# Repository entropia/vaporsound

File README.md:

# vaporsound

Our custom audio amplifier for the hackerspace

## hardware

The vaporsound board can drive two speakers with up to 50W each and has an analog stereo input.
It is connected to a beaglebone black which provides an ethernet port.
The vaporsound board needs a 24V power supply and provides 5V to the beaglebone black.

The hardware is designed in Eagle.

## mechanical

The vaporsound case is designed in Rhino3D and can be lasercut from 4mm wood.

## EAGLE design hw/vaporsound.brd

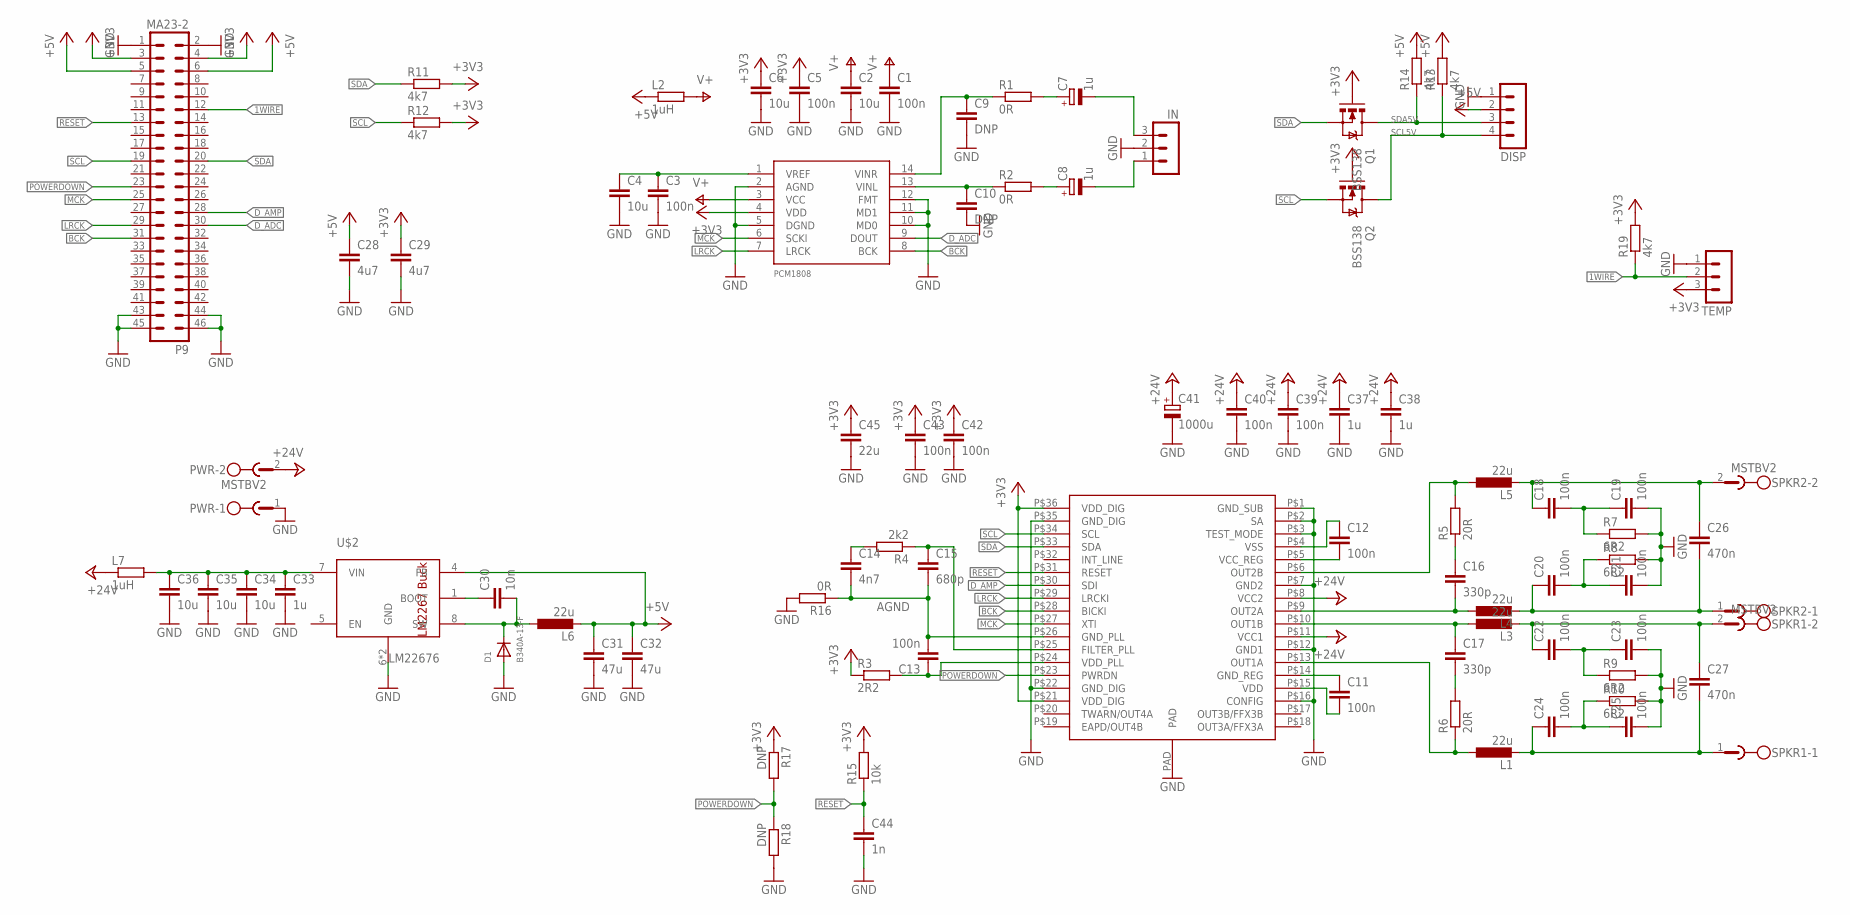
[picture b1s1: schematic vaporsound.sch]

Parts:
C1, C3, C5, C11, C12, C13, C18, C19, C20, C21, C22, C23, C24, C25, C39, C40, C42, C43: 100n; C0603
C2, C4, C6: 10u; C0805
C7, C8: 1u; E2-5
C9, C10: DNP; C0603
C14: 4n7; C0603
C15: 680p; C0603
C16, C17: 330p; C0603
C26, C27: 470n; C050-045X075
C28, C29: 4u7; C0805
C30: 10n; C0603
C31, C32: 47u; C1206
C33: 1u; C0805
C34, C35, C36: 10u; C1206
C37, C38: 1u; C1206
C41: 1000u; E5-10,5
C44: 1n; C0603
C45: 22u; C1206
D1: B340A-13-F; SMADIODE
DISP: MA04-1
IN: MA03-1
L1, L3, L4, L5: 22u; SRR1210
L2, L7: 1uH; R0805
L6: 22u; IHLP-3232DZ-11
P9: MA23-2
PWR: MSTBV2
Q1, Q2: BSS138; SOT23-3
R1, R2, R16: 0R; R0603
R3: 2R2; R0603
R4: 2k2; R0603
R5, R6: 20R; R1206
R7, R8, R9, R10: 6R2; R1206
R11, R12, R13, R14, R19: 4k7; R0603
R15: 10k; R0603
R17, R18: DNP; R0603
SPKR1, SPKR2: MSTBV2
TEMP: MA03-1
U$1: STA350BW; POWERSSO-36
U$2: LM22676; DDA0008B
U$3: PCM1808; TSSOP14

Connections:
1WIRE: P9.12, R19.1, TEMP.2
24V_DIGITAL: C33.1, C34.1, C35.1, C36.1, L7.2, U$2.7 (VIN)
+3V3: C5.1, C6.1, C29.1, C42.1, C43.1, C45.1, P9.3, P9.4, Q1.1 (G), Q2.1 (G), R3.1, R11.2, R12.2, R15.2, R17.1, R19.2, TEMP.3, U$1.P$21 (VDD_DIG), U$1.P$36 (VDD_DIG), U$3.4 (VDD)
+5V: C28.1, C31.1, C32.1, DISP.2, L2.1, L6.P$2 (2), P9.5, P9.6, R13.2, R14.2, U$2.4 (FB)
+24V: C37.1, C38.1, C39.1, C40.1, C41.+, L7.1, PWR.2, U$1.P$8 (VCC2), U$1.P$11 (VCC1)
ADC_VREF: C3.1, C4.1, U$3.1 (VREF)
AGND: C13.2, C14.2, C15.2, R16.1, U$1.P$26 (GND_PLL)
BCK: P9.31, U$1.P$28 (BICKI), U$3.8 (BCK)
BOOST: C30.1, U$2.1 (BOOT)
C_LEFT: C8.+, R2.2
C_RIGHT: C7.+, R1.2
D_ADC: P9.30, U$3.9 (DOUT)
D_AMP: P9.28, U$1.P$30 (SDI)
FILTER_PLL: C15.1, R4.1, U$1.P$25 (FILTER_PLL)
GND: C1.2, C2.2, C3.2, C4.2, C5.2, C6.2, C9.2, C10.2, C19.2, C21.2, C23.2, C25.2, C28.2, C29.2, C31.2, C32.2, C33.2, C34.2, C35.2, C36.2, C37.2, C38.2, C39.2, C40.2, C41.-, C42.2, C43.2, C44.2, C45.2, D1.A, DISP.1, IN.2, P9.1, P9.2, P9.43, P9.44, P9.45, P9.46, PWR.1, R7.2, R8.2, R9.2, R10.2, R16.2, R18.2, TEMP.1, U$1.P$1 (GND_SUB), U$1.P$2 (SA), U$1.P$3 (TEST_MODE), U$1.P$7 (GND2), U$1.P$12 (GND1), U$1.P$16 (CONFIG), U$1.P$22 (GND_DIG), U$1.P$35 (GND_DIG), U$1.PAD, U$2.6 (GND), U$2.EPAD (GND), U$3.2 (AGND), U$3.5 (DGND), U$3.10 (MD0), U$3.11 (MD1), U$3.12 (FMT)
GND_REG: C11.1, U$1.P$14 (GND_REG)
LEFT_INPUT: C8.-, IN.1
LRCK: P9.29, U$1.P$29 (LRCKI), U$3.7 (LRCK)
MCK: P9.25, U$1.P$27 (XTI), U$3.6 (SCKI)
unnamed: C17.2, R6.2
unnamed: C14.1, R4.2
unnamed: C16.1, R5.1
unnamed: C18.2, C19.1, R7.1
unnamed: C20.2, C21.1, R8.1
unnamed: C24.2, C25.1, R10.1
unnamed: C22.2, C23.1, R9.1
OUT1A: L1.P$1 (1), R6.1, U$1.P$13 (OUT1A)
OUT1B: C17.1, L3.P$1 (1), U$1.P$10 (OUT1B)
OUT2A: C16.2, L4.P$1 (1), U$1.P$9 (OUT2A)
OUT2B: L5.P$1 (1), R5.2, U$1.P$6 (OUT2B)
POWERDOWN: P9.23, R17.2, R18.1, U$1.P$23 (PWRDN)
RESET: C44.1, P9.13, R15.1, U$1.P$31 (RESET)
RIGHT_INPUT: C7.-, IN.3
SCL: P9.19, Q2.2 (S), R12.1, U$1.P$34 (SCL)
SCL5V: DISP.4, Q2.3 (D), R13.1
SDA: P9.20, Q1.2 (S), R11.1, U$1.P$33 (SDA)
SDA5V: DISP.3, Q1.3 (D), R14.1
SPKR1A: C24.1, C27.2, L1.P$2 (2), SPKR1.1
SPKR1B: C22.1, C27.1, L3.P$2 (2), SPKR1.2
SPKR2A: C20.1, C26.2, L4.P$2 (2), SPKR2.1
SPKR2B: C18.1, C26.1, L5.P$2 (2), SPKR2.2
SW: C30.2, D1.C, L6.P$1 (1), U$2.8 (SW)
V+: C1.1, C2.1, L2.2, U$3.3 (VCC)
VCC_REG: C12.2, U$1.P$5 (VCC_REG)
VDD: C11.2, U$1.P$15 (VDD)
VDD_PLL: C13.1, R3.2, U$1.P$24 (VDD_PLL)
VIN_L: C10.1, R2.1, U$3.13 (VINL)
VIN_R: C9.1, R1.1, U$3.14 (VINR)
VSS: C12.1, U$1.P$4 (VSS)

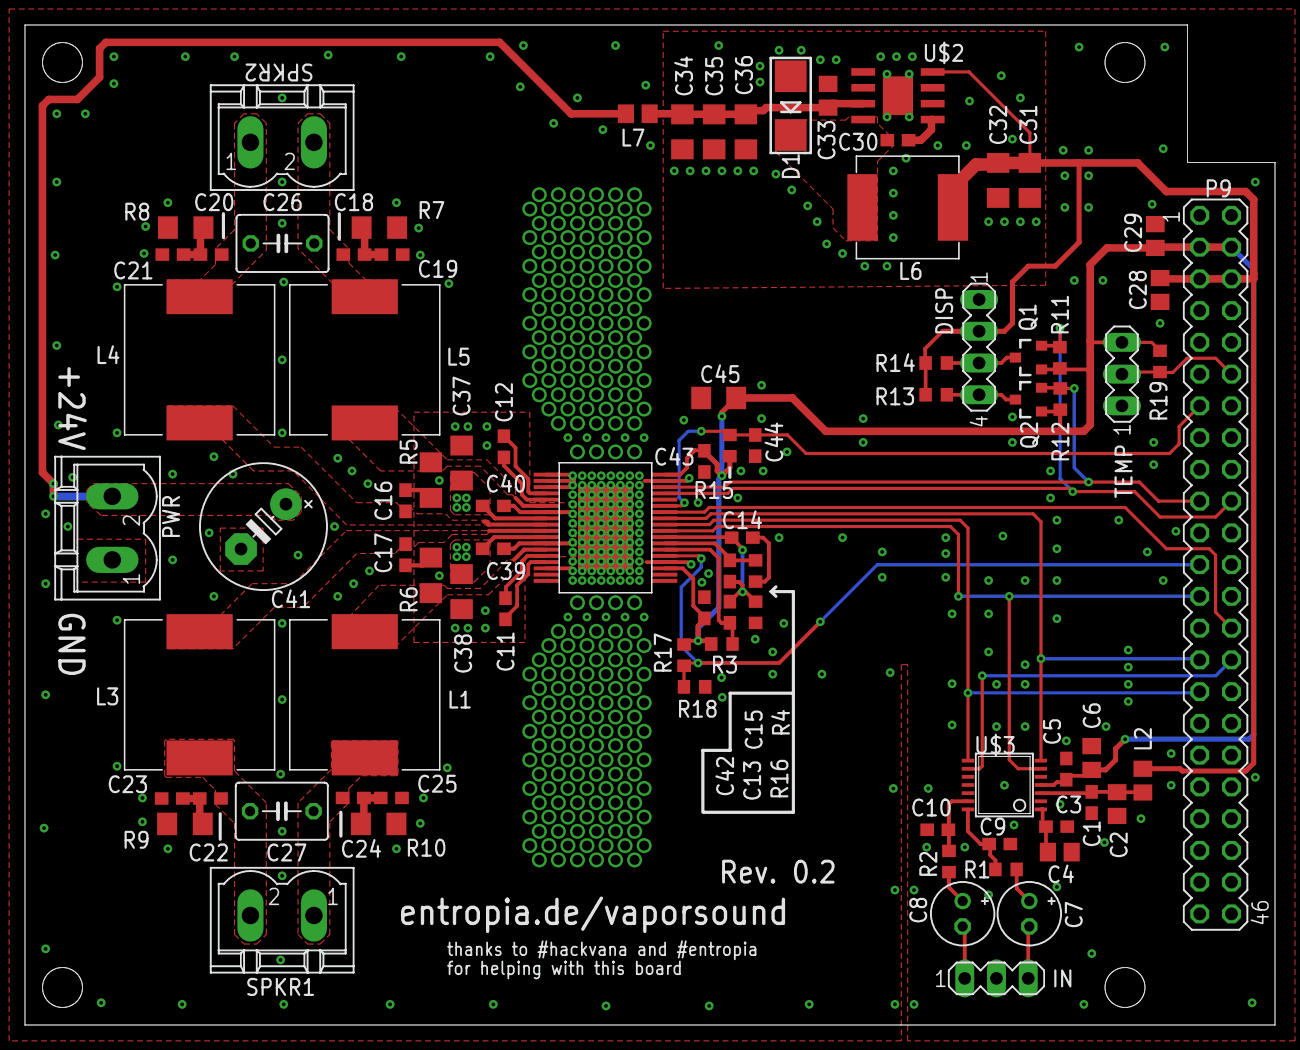
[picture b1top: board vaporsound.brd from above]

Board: 2 copper layers, 100.0 x 80.0 mm, 84 parts (0 on the bottom side), 49 nets.

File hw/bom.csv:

;Part;Value;Device;Package;Description;MF;MPN;OC_FARNELL;OC_NEWARK;PROD_ID
X;R1;0R;R-EU_R0603;R0603;RESISTOR, European symbol;;;;;
X;R2;0R;R-EU_R0603;R0603;RESISTOR, European symbol;;;;;
X;R16;0R;R-EU_R0603;R0603;RESISTOR, European symbol;;;;;
X;C41;1000u;CPOL-EUE5-10.5;E5-10,5;POLARIZED CAPACITOR, European symbol;;;;;
vorhanden;C1;100n;C-EUC0603;C0603;CAPACITOR, European symbol;;;;;
vorhanden;C3;100n;C-EUC0603;C0603;CAPACITOR, European symbol;;;;;
vorhanden;C5;100n;C-EUC0603;C0603;CAPACITOR, European symbol;;;;;
vorhanden;C11;100n;C-EUC0603;C0603;CAPACITOR, European symbol;;;;;
vorhanden;C12;100n;C-EUC0603;C0603;CAPACITOR, European symbol;;;;;
vorhanden;C13;100n;C-EUC0603;C0603;CAPACITOR, European symbol;;;;;
vorhanden;C18;100n;C-EUC0603;C0603;CAPACITOR, European symbol;;;;;
vorhanden;C19;100n;C-EUC0603;C0603;CAPACITOR, European symbol;;;;;
vorhanden;C20;100n;C-EUC0603;C0603;CAPACITOR, European symbol;;;;;
vorhanden;C21;100n;C-EUC0603;C0603;CAPACITOR, European symbol;;;;;
vorhanden;C22;100n;C-EUC0603;C0603;CAPACITOR, European symbol;;;;;
vorhanden;C23;100n;C-EUC0603;C0603;CAPACITOR, European symbol;;;;;
vorhanden;C24;100n;C-EUC0603;C0603;CAPACITOR, European symbol;;;;;
vorhanden;C25;100n;C-EUC0603;C0603;CAPACITOR, European symbol;;;;;
vorhanden;C39;100n;C-EUC0603;C0603;CAPACITOR, European symbol;;;;;
vorhanden;C40;100n;C-EUC0603;C0603;CAPACITOR, European symbol;;;;;
vorhanden;C42;100n;C-EUC0603;C0603;CAPACITOR, European symbol;;;;;
vorhanden;C43;100n;C-EUC0603;C0603;CAPACITOR, European symbol;;;;;
vorhanden;R15;10k;R-EU_R0603;R0603;RESISTOR, European symbol;;;;;
vorhanden;R1;10k;R-EU_R0805;R0805;RESISTOR, European symbol;;;;;
vorhanden;R2;10k;R-EU_R0805;R0805;RESISTOR, European symbol;;;;;
vorhanden;R3;10k;R-EU_R0805;R0805;RESISTOR, European symbol;;;;;
vorhanden;R4;10k;R-EU_R0805;R0805;RESISTOR, European symbol;;;;;
vorhanden;R5;10k;R-EU_R0805;R0805;RESISTOR, European symbol;;;;;
X;C30;10n;C-EUC0603;C0603;CAPACITOR, European symbol;;;;;
X;C2;10u;C-EUC0805;C0805;CAPACITOR, European symbol;;;;;
X;C4;10u;C-EUC0805;C0805;CAPACITOR, European symbol;;;;;
X;C6;10u;C-EUC0805;C0805;CAPACITOR, European symbol;;;;;
X;C34;10u;C-EUC1206;C1206;CAPACITOR, European symbol;;;;;
X;C35;10u;C-EUC1206;C1206;CAPACITOR, European symbol;;;;;
X;C36;10u;C-EUC1206;C1206;CAPACITOR, European symbol;;;;;
X;C44;1n;C-EUC0603;C0603;CAPACITOR, European symbol;;;;;
X;C7;1u;CPOL-EUE2-5;E2-5;POLARIZED CAPACITOR, European symbol;;;;;
X;C8;1u;CPOL-EUE2-5;E2-5;POLARIZED CAPACITOR, European symbol;;;;;
X;C33;1u;C-EUC0805;C0805;CAPACITOR, European symbol;;;;;
X;C37;1u;C-EUC1206;C1206;CAPACITOR, European symbol;;;;;
X;C38;1u;C-EUC1206;C1206;CAPACITOR, European symbol;;;;;
X;L2;1uH;R-EU_R0805;R0805;RESISTOR, European symbol;;;;;
X;L7;1uH;R-EU_R0805;R0805;RESISTOR, European symbol;;;;;
X;R5;20R;R-EU_R1206;R1206;RESISTOR, European symbol;;;;;
X;R6;20R;R-EU_R1206;R1206;RESISTOR, European symbol;;;;;
X;C45;22u;C-EUC1206;C1206;CAPACITOR, European symbol;;;;;
X;L1;22u;L-EUSRR1210;SRR1210;INDUCTOR, European symbol;;;;;
X;L3;22u;L-EUSRR1210;SRR1210;INDUCTOR, European symbol;;;;;
X;L4;22u;L-EUSRR1210;SRR1210;INDUCTOR, European symbol;;;;;
X;L5;22u;L-EUSRR1210;SRR1210;INDUCTOR, European symbol;;;;;
X;L6;22u;L-EUIHLP-3232DZ-11;IHLP-3232DZ-11;INDUCTOR, European symbol;;;;;
X;R4;2k2;R-EU_R0603;R0603;RESISTOR, European symbol;;;;;
X;R3;2R2;R-EU_R0603;R0603;RESISTOR, European symbol;;;;;
X;C16;330p;C-EUC0603;C0603;CAPACITOR, European symbol;;;;;
X;C17;330p;C-EUC0603;C0603;CAPACITOR, European symbol;;;;;
X;R6;330R;R-EU_R0805;R0805;RESISTOR, European symbol;;;;;
X;C26;470n;C-EU050-045X075;C050-045X075;CAPACITOR, European symbol;;;;;
X;C27;470n;C-EU050-045X075;C050-045X075;CAPACITOR, European symbol;;;;;
X;C31;47u;C-EUC1206;C1206;CAPACITOR, European symbol;;;;;
X;C32;47u;C-EUC1206;C1206;CAPACITOR, European symbol;;;;;
X;R11;4k7;R-EU_R0603;R0603;RESISTOR, European symbol;;;;;
X;R12;4k7;R-EU_R0603;R0603;RESISTOR, European symbol;;;;;
X;R13;4k7;R-EU_R0603;R0603;RESISTOR, European symbol;;;;;
X;R14;4k7;R-EU_R0603;R0603;RESISTOR, European symbol;;;;;
X;R19;4k7;R-EU_R0603;R0603;RESISTOR, European symbol;;;;;
X;C14;4n7;C-EUC0603;C0603;CAPACITOR, European symbol;;;;;
X;C28;4u7;C-EUC0805;C0805;CAPACITOR, European symbol;;;;;
X;C29;4u7;C-EUC0805;C0805;CAPACITOR, European symbol;;;;;
X;C15;680p;C-EUC0603;C0603;CAPACITOR, European symbol;;;;;
X;R7;6R2;R-EU_R1206;R1206;RESISTOR, European symbol;;;;;
X;R8;6R2;R-EU_R1206;R1206;RESISTOR, European symbol;;;;;
X;R9;6R2;R-EU_R1206;R1206;RESISTOR, European symbol;;;;;
X;R10;6R2;R-EU_R1206;R1206;RESISTOR, European symbol;;;;;
X;D1;B340A-13-F;DIODESMA;SMADIODE;Diode;;;;;
X;T1;BC847C;BC847A-NPN-SOT23-BEC;SOT23-BEC;NPN Transistror;;;;;
X;Q1;BSS138;MOSFET-NCHANNELBSS138;SOT23-3;Common NMOSFET Parts;;;;;TRANS-00830
X;Q2;BSS138;MOSFET-NCHANNELBSS138;SOT23-3;Common NMOSFET Parts;;;;;TRANS-00830
;C9;DNP;C-EUC0603;C0603;CAPACITOR, European symbol;;;;;
;C10;DNP;C-EUC0603;C0603;CAPACITOR, European symbol;;;;;
;R17;DNP;R-EU_R0603;R0603;RESISTOR, European symbol;;;;;
;R18;DNP;R-EU_R0603;R0603;RESISTOR, European symbol;;;;;
X;SW1;EC12E_SW;EC12E_SW;ALPS_EC12E_SW;ALPS rotary Encoder EC12E series with switch;;EC12E2424407;1520813;74M1068;
X;U$2;LM22676;LM2267_123;DDA0008B;LM2267x;;;;;
X;P9;MA23-2;MA23-2;MA23-2;;;;;;
X;P8;MA23-2;MA23-2;MA23-2;;;;;;
X;PWR;MSTBV2;MSTBV2;MSTBV2;PHOENIX;;MSTBV 2,5/2-GF-5.08;1792792;69R9845;
X;SPKR1;MSTBV2;MSTBV2;MSTBV2;PHOENIX;;MSTBV 2,5/2-GF-5.08;1792792;69R9845;
X;SPKR2;MSTBV2;MSTBV2;MSTBV2;PHOENIX;;MSTBV 2,5/2-GF-5.08;1792792;69R9845;
X;U$3;PCM1808;PCM1808;TSSOP14;;;;;;
X;U$1;STA350BW;STA350BW;POWERSSO-36;;;;;;
X;DISP;;MA04-1;MA04-1;PIN HEADER;;;unknown;unknown;
X;IN;;MA03-1;MA03-1;PIN HEADER;;;unknown;unknown;
X;TEMP;;MA03-1;MA03-1;PIN HEADER;;;unknown;unknown;
X;ENCODER;;PINHD-1X4/90;1X04/90;PIN HEADER;;;;;
X;PWN_BTN_LED;;PINHD-1X4/90;1X04/90;PIN HEADER;;;;;
X;PWR_CON;;PINHD-1X2/90;1X02/90;PIN HEADER;;;;;
X;JP1;;PINHD-1X4/90;1X04/90;PIN HEADER;;;;;
X;LED1;;LED3MM;LED3MM;LED;;;;;
X;S1;;40-XX;B3F-40XX;OMRON SWITCH;OMRON COMPONENTS USA;B3F-4000;176434;36K3105;
X;JP1;;PINHD-1X4/90;1X04/90;PIN HEADER;;;;;

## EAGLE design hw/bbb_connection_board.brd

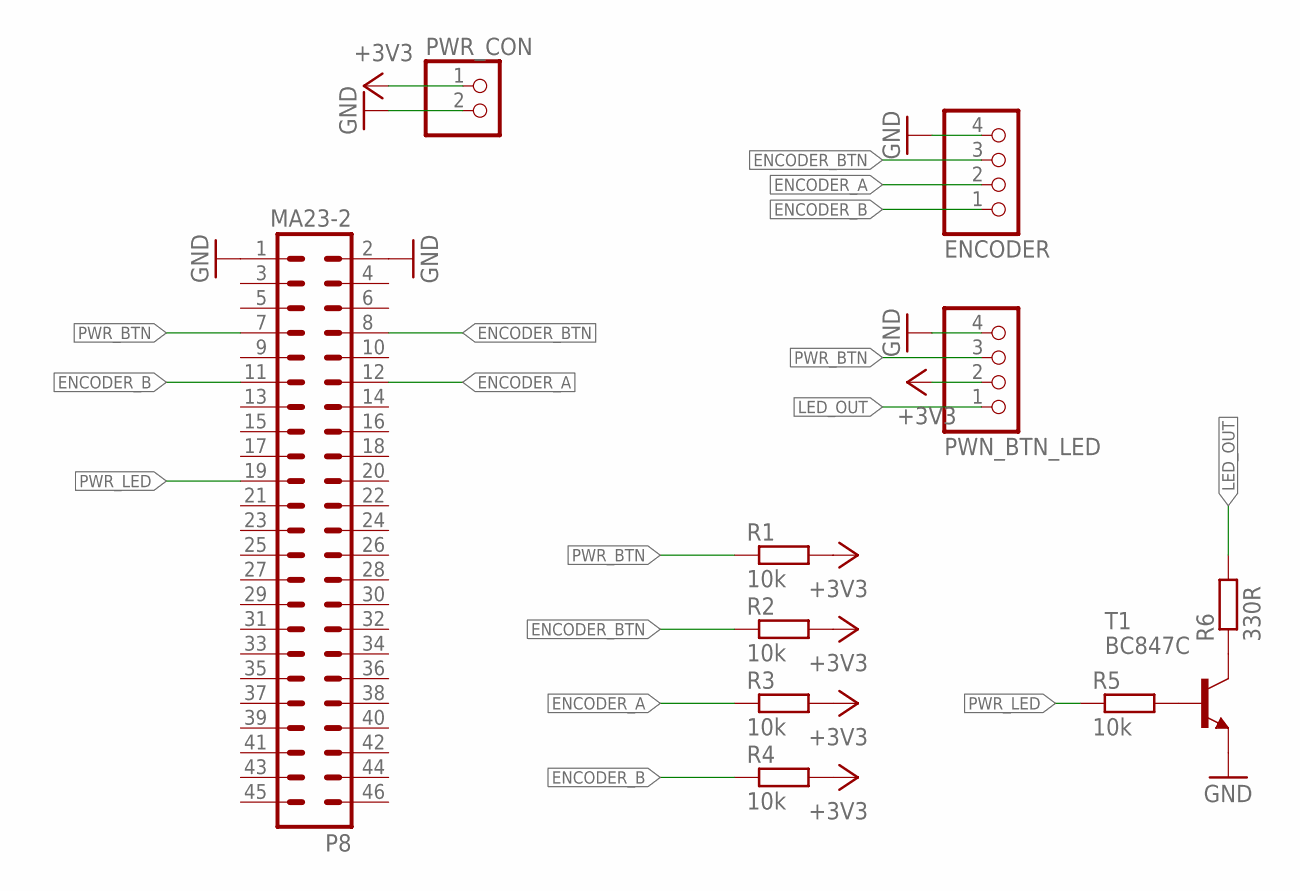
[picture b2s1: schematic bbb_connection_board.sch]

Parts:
ENCODER: PINHD-1X4/90; 1X04/90
P8: MA23-2
PWN_BTN_LED: PINHD-1X4/90; 1X04/90
PWR_CON: PINHD-1X2/90; 1X02/90
R1, R2, R3, R4, R5: 10k; R0805
R6: 330R; R0805
T1: BC847C; SOT23-BEC

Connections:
+3V3: PWN_BTN_LED.2, PWR_CON.1, R1.2, R2.2, R3.2, R4.2
ENCODER_A: ENCODER.2, P8.12, R3.1
ENCODER_B: ENCODER.1, P8.11, R4.1
ENCODER_BTN: ENCODER.3, P8.8, R2.1
GND: ENCODER.4, P8.1, P8.2, PWN_BTN_LED.4, PWR_CON.2, T1.E
LED_OUT: PWN_BTN_LED.1, R6.2
unnamed: R5.2, T1.B
unnamed: R6.1, T1.C
PWR_BTN: P8.7, PWN_BTN_LED.3, R1.1
PWR_LED: P8.19, R5.1

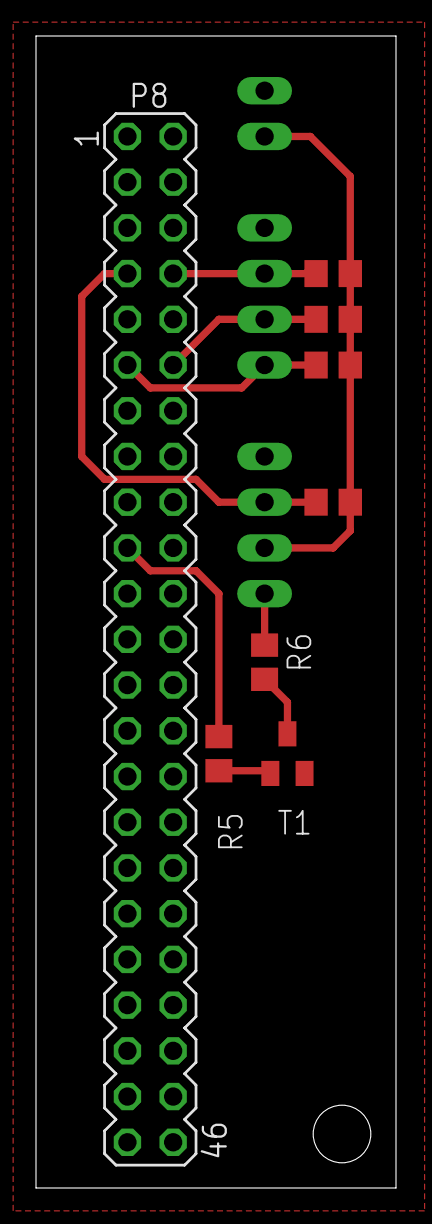
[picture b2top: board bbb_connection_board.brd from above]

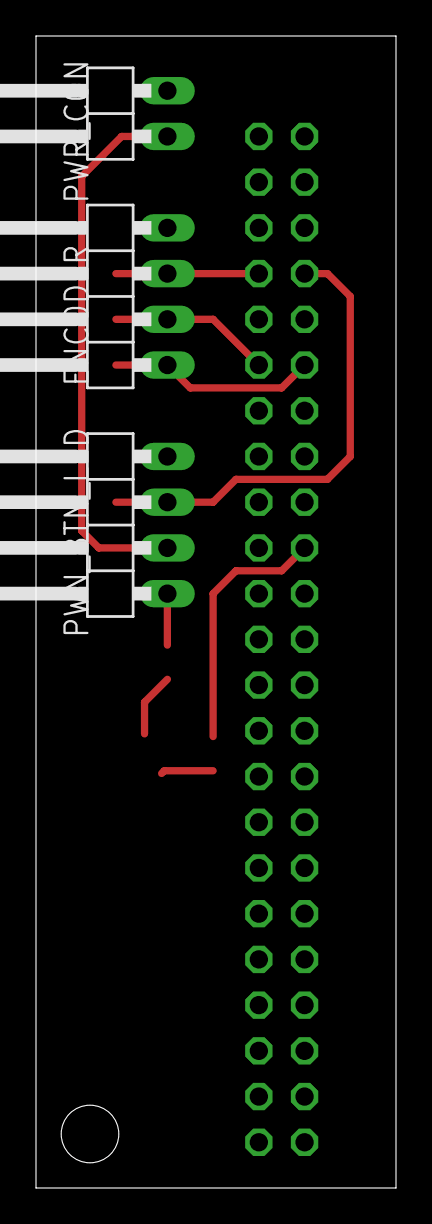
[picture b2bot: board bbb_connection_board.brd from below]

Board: 2 copper layers, 20.0 x 64.0 mm, 11 parts (3 on the bottom side), 10 nets.

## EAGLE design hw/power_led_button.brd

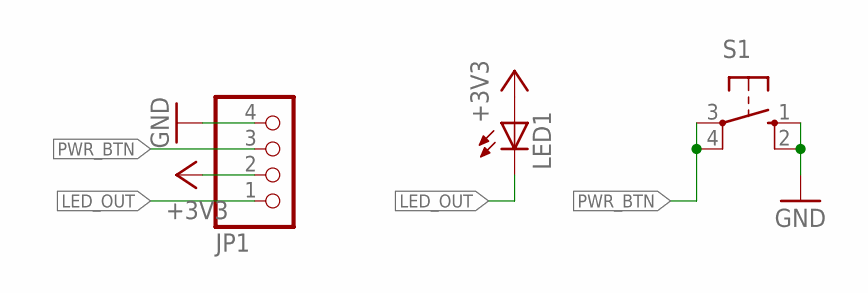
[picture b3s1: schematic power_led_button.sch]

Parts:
JP1: PINHD-1X4/90; 1X04/90
LED1: LED3MM
S1: 40-XX; B3F-40XX

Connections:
+3V3: JP1.2, LED1.A
GND: JP1.4, S1.1 (S), S1.2 (S1)
LED_OUT: JP1.1, LED1.K (C)
PWR_BTN: JP1.3, S1.3, S1.4 (P1)

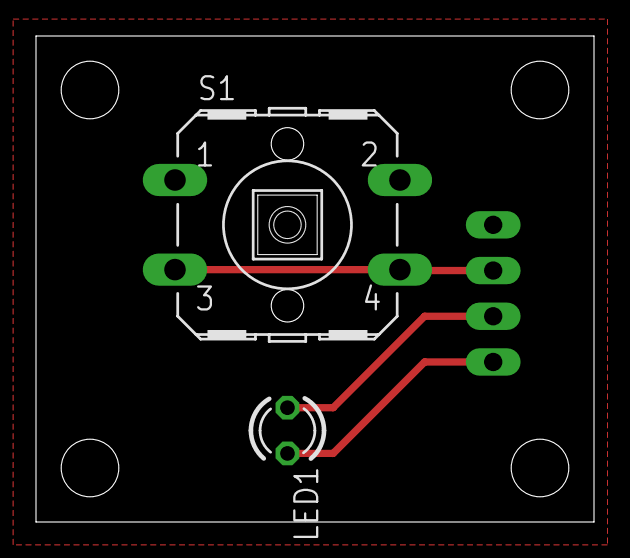
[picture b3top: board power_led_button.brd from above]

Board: 2 copper layers, 31.0 x 27.0 mm, 3 parts (1 on the bottom side), 4 nets.

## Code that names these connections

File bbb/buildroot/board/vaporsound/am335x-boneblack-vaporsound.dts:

/dts-v1/;

#include "am33xx.dtsi"
#include "am335x-bone-common.dtsi"

/ {
	model = "TI AM335x BeagleBone Black";
	compatible = "ti,am335x-bone-black", "ti,am335x-bone", "ti,am33xx";
};

&ldo3_reg {
	regulator-min-microvolt = <1800000>;
	regulator-max-microvolt = <1800000>;
	regulator-always-on;
};

&mmc1 {
	vmmc-supply = <&vmmcsd_fixed>;
};

&gpio1 {
	/* EMMC in reset */
	emmc_rst {
		gpio-hog;
		gpios = <20 0>;
		output-high;
		line-name = "EMMC ResetN";
	};

	/* i2s master clock is always on */
	i2s_mclk_on {
		gpio-hog;
		gpios = <27 0>;
		output-high;
		line-name = "I2S master clock on";
	};
};

&rtc {
	system-power-controller;
};

&am33xx_pinmux {
	/* audio */
	mcasp0_pins: mcasp0_pins {
		pinctrl-single,pins = <
			0x1ac (PIN_INPUT_PULLUP | MUX_MODE0)	/* mcasp0_ahclkx.mcasp0_ahclkx (MCK) */
			0x19c (PIN_OUTPUT_PULLDOWN | MUX_MODE2) /* mcasp0_ahclkr.mcasp0_axr2 (D_AMP) */
			0x194 (PIN_OUTPUT_PULLUP | MUX_MODE0)	/* mcasp0_fsx.mcasp0_fsx (LRCK) */
			0x190 (PIN_OUTPUT_PULLDOWN | MUX_MODE0)	/* mcasp0_aclkx.mcasp0_aclkx (BCK) */
			0x198 (PIN_INPUT_PULLUP | MUX_MODE0)    /* mcasp0_axr0.mcasp0_axr0 (D_ADC) */
			0x06c (PIN_OUTPUT_PULLDOWN | MUX_MODE7)	/* gpmc_a11.GPIO1_27 */

			0x074 (PIN_OUTPUT_PULLDOWN | MUX_MODE7) /* gpmc_wpn.GPIO0_31 (RESET) */
			0x044 (PIN_OUTPUT_PULLDOWN | MUX_MODE7) /* gpmc_a1.GPIO1_17 (POWERDOWN) */
		>;
	};

	/* rotary encoder */
	eqep2_pins: eqep2_pins {
		pinctrl-single,pins = <
			0x030 (PIN_INPUT_PULLUP | MUX_MODE4)    /* GPMC_AD12 -> eQEP2A_in (ENCODER_A) */
			0x034 (PIN_INPUT_PULLUP | MUX_MODE4)    /* GPMC_AD13 -> eQEP2B_in (ENCODER_B) */
		>;
	};

	/* PWM power led */
	ehrpwm2_pins: ehrpwm2_pins {
		pinctrl-single,pins = <
			0x020 (PIN_OUTPUT_PULLDOWN | MUX_MODE4) /* GPMC_AD8 -> ehrpwm2A (PWR_LED) */
		>;
	};
};

&epwmss2 {
	status = "okay";
};

&ehrpwm2 {
	pinctrl-names = "default";
	pinctrl-0 = <&ehrpwm2_pins>;

	status = "okay";
};

&eqep2 {
	pinctrl-names = "default";
	pinctrl-0 = <&eqep2_pins>;

	clocks = <&dpll_core_m4_div2_ck>;
	clock-names = "fck";

	status = "okay";
};

&lcdc {
	status = "okay";
};

&mcasp0	{
#sound-dai-cells = <0>;
	pinctrl-names = "default";
	pinctrl-0 = <&mcasp0_pins>;
	status = "okay";
	op-mode = <0>;	/* MCASP_IIS_MODE */
	tdm-slots = <2>;
	serial-dir = <	/* 0: INACTIVE, 1: TX, 2: RX */
			0 0 1 0 /* FIXME: axr0 inactive for now */
		>;
	tx-num-evt = <1>;
	rx-num-evt = <1>;
};

&i2c2 {
	clock-frequency = <10000>;

	sta350: sta350@38 {
		#sound-dai-cells = <0>;
		compatible = "st,sta350";
		reg = <0x1c>;
		reset-gpios = <&gpio0 31 0>;
		power-down-gpios = <&gpio1 17 0>;

		vdd-dig-supply = <&fixed_internal_supply>;
		vdd-pll-supply = <&fixed_internal_supply>;
		vcc-supply = <&fixed_external_supply>;

		st,max-power-correction;
		st,distortion-compensation;
		st,noise-shape-dc-cut;
	};
};

/ {
	sound {
		compatible = "simple-audio-card";
		simple-audio-card,name = "Vaporsound";
		simple-audio-card,widgets =
			"Speaker", "Speaker";
		simple-audio-card,routing =
			"Speaker", "Playback";
		simple-audio-card,format = "i2s";
		simple-audio-card,bitclock_master = <&sound_codec>;
		simple-audio-card,frame_master = <&sound_cpu>;

		sound_cpu: simple-audio-card,cpu {
			sound-dai = <&mcasp0>;
			system-clock-frequency = <24576000>;
		};

		sound_codec: simple-audio-card,codec {
			sound-dai = <&sta350>;
			system-clock-frequency = <24576000>;
		};
	};

	fixed_external_supply: fixed-regulator {
		compatible = "regulator-fixed";
		regulator-name = "vaporsound_supply";
	};

	fixed_internal_supply: fixed-regulator {
		compatible = "regulator-fixed";
		regulator-name = "vaporsound_internal_supply";
	};
};

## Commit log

2015-06-24 initial schematic draft
2015-06-29 schematics done-ish
2015-07-06 add sta350bw datasheet etc
2015-07-06 layout voltage regulator and add some capacitors
2015-07-06 add gitignore
2015-07-06 add gerbers of eval board
2015-07-06 modify footprint so it can be produced without additional fee
    minimal distance between traces should be 6mil
2015-07-06 begin layout of 24v side of sta350
2015-07-06 output stage almost routed
2015-07-07 begin component placement at input side of sta350
2015-07-09 add thermal vias for sta350
2015-07-09 use 0603 capacitors instead of 0402 ones
    0603 is small enough for the board
2015-07-09 move part libraries to subfolder
    makes it easier to include the project-specific libraries in eagle
2015-07-10 do some more floorplanning
2015-07-10 output stage fully routed, adc routed
2015-07-12 board fully routed
2015-07-12 fix wrong angles
2015-07-12 Add pullup and pulldown STA350BW + minor layout fixes
2015-07-12 Reroute I2S connections
2015-07-12 ground plane stitching + thermal vias
2015-07-12 silkscreen
2015-07-13 some more silkscreen fixes
2015-07-13 changes for easier manufacturability
    minimum trace width 8mil
    minimum clearance 7mil (8mil except the sta350bw)
2015-07-13 add more thermal vias
2015-07-13 slightly move the sta350 to the lower end of the pcb
2015-07-13 add inductor name to silkscreen
2015-07-13 move reset to different bbb pin and remove pull-down resistor
    reset of the sta350 is now connected to a pin with pull-up on the bbb instead of one with a pull-down
2015-07-13 remove soldermask and move some passives to be able to solder a heatsink to the board
2015-07-14 add 1wire temperature sensor + some thermal optimizations
2015-07-14 add some greetings on the silkscreen
2015-07-14 move resistors a bit away from the heatsink
2015-07-15 begin second board plugged onto the bbb
    pin mapping definitions
2015-07-16 schematic of bbb connection board
2015-07-17 bbb connection board routed
2015-07-17 update gitignore to ignore eagle backup files also in subfolders of hw/
2015-07-17 add encoder board
2015-07-17 move connectors to bottom layer
    the connector to the bbb also needs to be mounted on the bottom side, but can't be simply mirrored, since that would change the pinout
2015-07-17 use angled pinheaders
2015-07-17 add power button and power led board
2015-07-19 add missing values
2015-07-25 route last unrouted trace and increase version number
2015-08-07 minor groundplane fix
2015-10-21 add FLIR images
2016-05-14 add case design for laser cutting
    use 4mm wood for the case
2016-06-18 use eudev
2016-06-18 use initrd instead of ram overlay
2016-06-18 add shairport-sync config
2016-06-18 change issue
2016-06-18 init: abort on failure
2016-06-18 use watchdog
2016-06-18 buildroot: set root pw
2016-06-18 add initial buildroot
2016-06-18 add initialization framework
2016-06-18 only generate uncompressed initramfs
2016-06-18 use ttyS instead of ttyO
2016-06-18 fix ram-overlay build def
2016-06-18 disallow pulseaudio exit/module-loading
2016-06-18 buildroot: enable espeak, mpd, shairport-sync
2016-06-18 fix uboot patch path
2016-06-18 build root as initrd
2016-06-18 init: fix banner tail offset
2016-06-18 clean up uenv
2016-06-18 remove fixed name from shairport config
2016-06-18 use ccache
2016-06-18 fix uenv
2016-06-18 fix uboot autoboot
2016-06-18 override console setting (ttyO0 is deprecated)
2016-06-18 more config
2016-06-18 add overlay directories to rootfs-skeleton
2016-06-18 use current uboot
2016-06-18 enable serial getty
2016-06-18 add RAM overlay tool
2016-06-18 ram-overlay: only /dev mount exists at early boot
2016-06-18 build rsync
2016-06-18 call mount_ram_overlay in inittab
2016-06-18 fixes
2016-06-18 run mpd, PA, shairport via runit
2016-06-18 build strace:
2016-06-18 build libmpdclient for database proxy support
2016-06-18 move init script
    /sys needs to be mounted to detect the mac address
2016-06-18 limit pcm1808 rates for 24,576 mhz clock
2016-06-18 stop BBB from blinking annoyingly
2016-06-18 build kernel with debug foo
2016-06-18 fix usb support
2016-06-18 order kernel patches
2016-06-18 fix inittab
2016-06-18 pulseaudio: enable zeroconf
2016-06-18 build some more packages
2016-06-18 make bash the default shell
2016-06-18 build pcm1808 as a module
2016-06-18 init: create resolv.conf
    fixes ntp sync
2016-06-18 init: remove /etc/resolv.conf before recreating it
    the skeleton links /etc/resolv.conf to /tmp, which gets overmounted
    later in the boot process.
    As / is in RAM and completely writeable anyway, we remove the symlink.
2016-06-18 allow module loading in pulseaudio
    this is necessary for hotplugging
2016-06-18 add config file to make /boot stay RW for development
2016-06-18 busybox: include pstree
2016-06-18 dynamically configure shairport-sync for shorter sink names
2016-06-18 configure rotary encoder and pwm
2016-06-18 build nginx
2016-06-18 add mpd configuration script
2016-06-18 disable mpd, PA, shairport
2016-06-18 generate firmware-version file
2016-06-18 pulseaudio: force vaporsound to be the default output
2016-06-18 buildroot: remove overlay dirs
2016-06-18 add rngd
2016-06-18 enable more alsa utils
2016-06-18 more init script work
2016-06-18 add pcm1808 foo
2016-06-18 make init-overrides executable
2016-06-18 run runsvdir from inittab
2016-06-18 fix eqep direction
2016-06-18 uboot: remove bootdelay patch
    Patch is upstream as of buildroot 2016.05
2016-06-18 dt/mcasp0: enable axr0
2016-06-18 add busybox defconfig
2016-06-18 add vaporctl
2016-06-18 add webui
2016-06-19 fix image id generation
2016-06-19 vaporctl: api registration
2016-06-19 add vaporctl to defconfig
2016-06-19 build debugging utils
2016-06-19 sanitize prompt
2016-06-19 conserve space
2016-06-19 slim down linux build
2016-06-19 build mpd with http support
2016-06-19 build ubus
2016-06-19 vaporctl
2016-06-19 vaporui
2016-08-06 create merged BOM of all boards
2016-08-07 use dmix
2016-09-28 add webui html foo
2016-09-28 webui: explicitly specify ajax data type
    Fixes NaN error in firefox
2016-10-18 add information about the hardware and case to README.md
2017-02-24 preinit: add rc.local suppport
    Allow applying custom hacks during early bootup via an rc.local-style
    script.
2017-02-26 update for buildroot 2016.11.2
    Add an "external.desc" file and modify references to BR2_EXTERNAL
    accordingly to comply with the new buildroot requirements for external
    overlays.
2017-03-22 downgrading interpolation of shairport to avoid resyncs

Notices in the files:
parts and their libraries:
mircobuilder: This work is placed in the public domain, and may be freely used for commercial and non-commercial work with the following conditions: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
SparkFun-DiscreteSemi: Licensing: Creative Commons ShareAlike 4.0 International - https://creativecommons.org/licenses/by-sa/4.0
